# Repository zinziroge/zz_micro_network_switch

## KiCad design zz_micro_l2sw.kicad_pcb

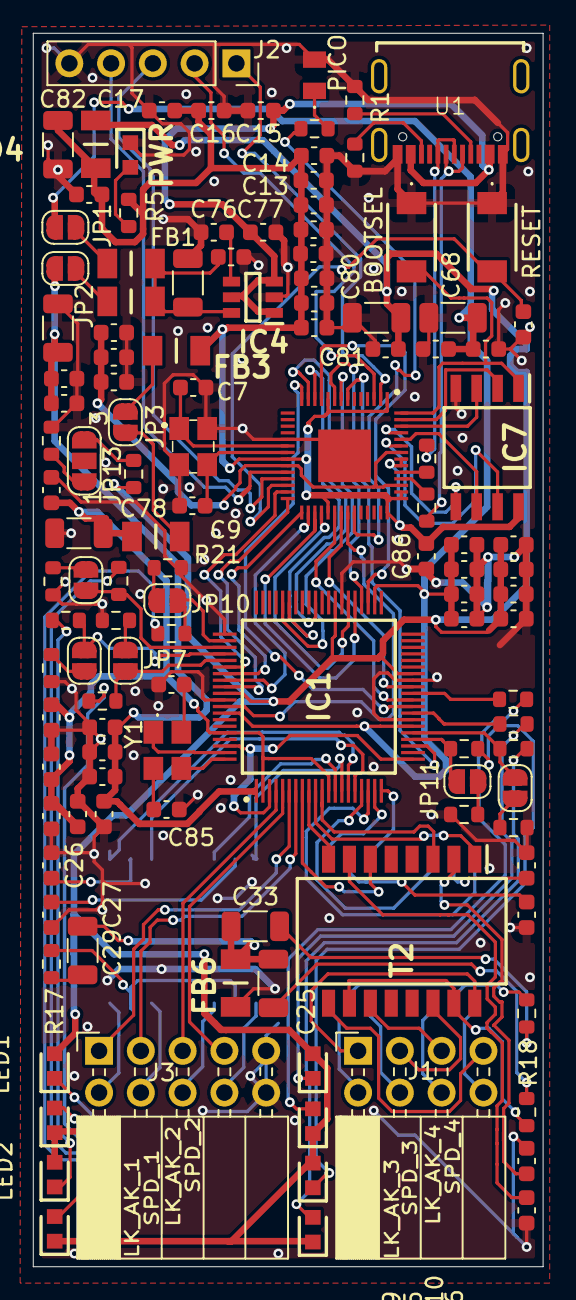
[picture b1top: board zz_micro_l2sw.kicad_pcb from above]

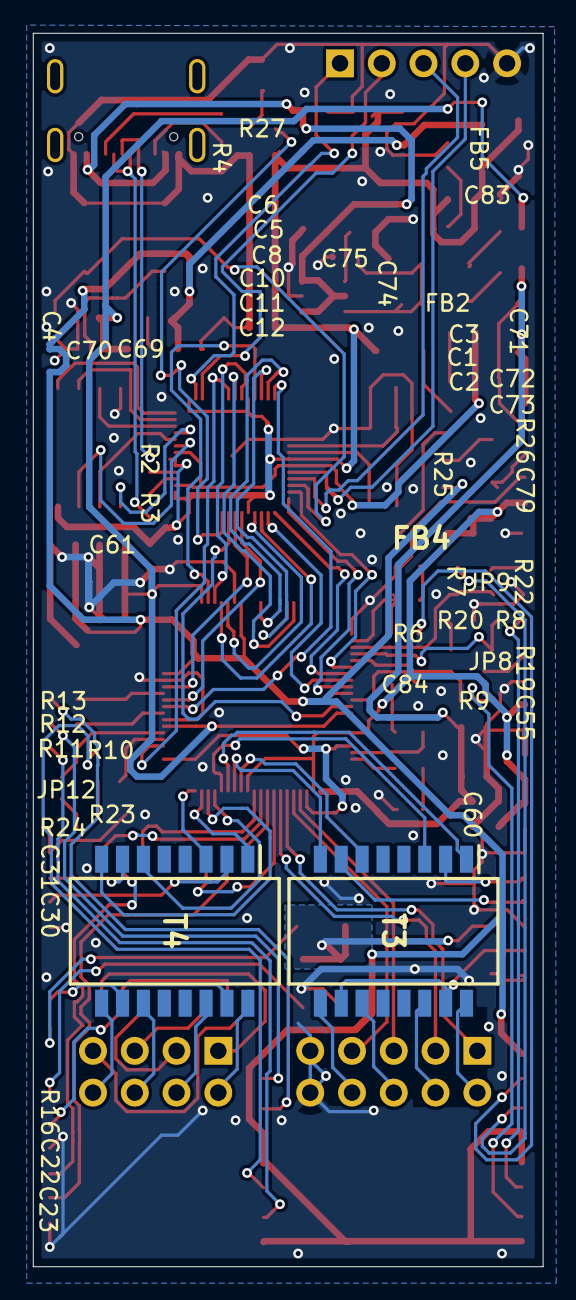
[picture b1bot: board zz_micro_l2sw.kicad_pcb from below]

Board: 2 copper layers, 31.0 x 75.0 mm, 127 parts (2 on the bottom side), 122 nets.

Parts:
C1, C2, C4, C6, C8, C10, C11, C12, C13, C14, C86: 100nF; C_0603_1608Metric
C3, C5: 1uF; C_0603_1608Metric
C7, C9: 18pF; C_0603_1608Metric
C15, C16, C17: 10uF; C_0603_1608Metric
C22, C23, C26, C27, C30, C52, C53, C54, C57, C58, C59, C62, C63, C64, C65, C66, C67, C69, C72, C75, C77, C79, C81, C83: 0.1uF; C_0603_1608Metric
C25, C29, C33: 1nF/2kV; C_1206_3216Metric
C31: 0/1uF; C_0603_1608Metric
C55, C56, C60, C61: 22uF/6.3V; C_0603_1608Metric
C68, C71, C74, C78, C80, C82: 100uF/6.3V; C_1206_3216Metric
C70, C73, C76: 0.01uF; C_0603_1608Metric
C84, C85: 22pF; C_0603_1608Metric
FB1, FB2, FB3, FB4, FB5, FB6: HI1206N101R-00; BEADC3216X130N
IC1: KSZ8795CLXIC; QFP40P1200X1200X160-80N
IC4: MIC5309-1.2YD6; SOT95P280X100-6N
IC5: RP2040; QFN40P700X700X90-57N-D
IC7: W25Q128JVSIQ; SOIC127P790X216-8N
J1: Conn_02x04_Top_Bottom; PinSocket_2x04_P2.54mm_Horizontal
J2: Conn_01x05; PinSocket_1x05_P2.54mm_Vertical
J3: Conn_02x05_Top_Bottom; PinSocket_2x05_P2.54mm_Horizontal
JP1, JP2, JP3, JP7, JP8, JP9, JP10, JP11, JP12: SolderJumper-2_P1.3mm_Open_RoundedPad1.0x1.5mm
JP13: SolderJumper-3_P1.3mm_Open_RoundedPad1.0x1.5mm_NumberLabels
LED1: SPD_2; LEDC1608X70N
LED2: SPD_1; LEDC1608X70N
LED3: PICO; KT0805G
LED4: PWR; LEDC1608X70N
LED5: SPD_3; LEDC1608X70N
LED6: SPD_4; LEDC1608X70N
LED7: LK_AK_2; LEDC1608X70N
LED8: LK_AK_1; LEDC1608X70N
LED9: LK_AK_3; LEDC1608X70N
LED10: LK_AK_4; LEDC1608X70N
R1, R4: 5.1k; R_0603_1608Metric
R2, R3: 27; R_0603_1608Metric
R5, R6, R7, R8, R9, R10, R11, R12, R13, R27: 470; R_0603_1608Metric
R16, R17, R18: 75; R_0603_1608Metric
R19, R20, R21, R22, R23, R24: 750; R_0603_1608Metric
R25: 4.7k; R_0603_1608Metric
R26: 330; R_0603_1608Metric
S1: RESET; TS1088AR02016
S2: BOOTSEL; TS1088AR02016
T2, T3, T4: H1102NL; SOIC127P940X597-16N
U1: TYPE-C 16PIN 2MD(073)
Y1: X322525MOB4SI
Y4: 12MHz; X322512MSB4SI

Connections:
CRSDV5: IC1.51 (RXDV5/__CRSDV5/__RXD5_CTL), IC5.13 (GPIO10)
D_N: R3.1, U1.A7 (DN1), U1.B7 (DN2)
D_P: R2.1, U1.A6 (DP1), U1.B6 (DP2)
GND: C1.2, C2.2, C3.2, C4.1, C5.2, C6.2, C7.2, C8.2, C9.2, C10.2, C11.2, C12.2, C13.2, C14.2, C15.2, C16.2, C17.2, C22.2, C23.2, C26.2, C27.2, C30.2, C31.2, C52.2, C53.2, C54.2, C55.2, C56.2, C57.2, C58.2, C59.2, C60.2, C61.2, C62.2, C63.2, C64.2, C65.2, C66.2, C67.2, C68.2, C69.2, C70.2, C71.2, C72.2, C73.2, C74.2, C75.2, C76.2, C77.2, C78.2, C79.2, C80.2, C81.2, C82.2, C83.2, C84.2, C85.2, C86.2, FB6.1, IC1.27 (GNDD_1), IC1.33 (GNDD_2), IC1.47 (GNDD_3), IC1.61 (GNDD_4), IC1.71 (GNDD_5), IC4.2 (GND), IC5.19 (TESTEN), IC5.57 (GND), IC7.4 (GND), J2.5, J3.5, J3.10, LED3.2 (K), LED4.1 (K), R1.2, R4.2, R19.2, R20.2, R21.2, R22.2, R23.2, R24.2, R26.1, S1.1 (COM), S2.1 (COM), U1.A1 (GND_1), U1.B1 (GND_2), Y4.2 (GND_1), Y4.4 (GND_2)
GNDA: IC1.3 (GNDA_1), IC1.21 (GNDA_2), IC1.78 (GNDA_3)
GNDS: C25.2, C29.2, C33.2, FB6.2
INTR_N_KSZ8795: IC1.23 (INTR_N), IC5.7 (GPIO5)
KSZ8795_XI: IC1.79 (XI), Y1.1 (CRYSTAL__1)
KSZ8795_XO: IC1.80 (XO), Y1.3 (CRYSTAL__2)
LED1_0: IC1.65 (LED1_0), JP7.1 (A), R9.1
LED1_1: IC1.64 (LED1_1), JP8.1 (A), R8.1
LED2_0: IC1.63 (LED2_0), JP9.1 (A), R7.1
LED2_1: IC1.62 (LED2_1), JP10.1 (A), R6.1
LED3_0: IC1.25 (LED3_0), JP11.1 (A), R11.1
LED3_1: IC1.24 (LED3_1), JP12.1 (A), R10.1
LED4_0: IC1.31 (LED4_0), R13.1
LED4_1: IC1.28 (LED4_1), R12.1
unnamed: C25.1, R16.2
unnamed: C29.1, R17.2
unnamed: C33.1, R18.2
unnamed: C76.1, IC4.4 (BYP/ADJ)
unnamed: C74.1, C75.1, FB1.1, FB2.1, IC4.6 (VOUT)
unnamed: IC5.46 (USB_DM), R3.2
unnamed: IC5.47 (USB_DP), R2.2
unnamed: J1.1, T2.16 (TX+)
unnamed: J1.2, T2.14 (TX-)
unnamed: J1.3, T2.11 (RX+)
unnamed: J1.4, T2.9 (RX-)
unnamed: J1.5, T4.16 (TX+)
unnamed: J1.6, T4.14 (TX-)
unnamed: J1.7, T4.11 (RX+)
unnamed: J1.8, T4.9 (RX-)
unnamed: J3.6, T3.16 (TX+)
unnamed: J3.7, T3.14 (TX-)
unnamed: J3.8, T3.11 (RX+)
unnamed: J3.9, T3.9 (RX-)
unnamed: FB1.2, JP1.1 (A)
unnamed: FB2.2, JP2.1 (A)
unnamed: FB3.2, JP3.1 (A)
unnamed: FB4.1, JP3.2 (B)
unnamed: JP7.2 (B), R20.1
unnamed: JP8.2 (B), R19.1
unnamed: JP9.2 (B), R22.1
unnamed: JP10.2 (B), R21.1
unnamed: JP11.2 (B), R24.1
unnamed: JP12.2 (B), R23.1
unnamed: JP13.1 (A), R26.2
unnamed: JP13.3 (B), R25.1
unnamed: LED1.1 (K), R6.2
unnamed: LED2.1 (K), R8.2
unnamed: LED3.1 (A), R27.2
unnamed: LED4.2 (A), R5.2
unnamed: LED5.1 (K), R10.2
unnamed: LED6.1 (K), R12.2
unnamed: LED7.2 (K), R7.2
unnamed: LED8.2 (K), R9.2
unnamed: LED9.2 (K), R11.2
unnamed: LED10.2 (K), R13.2
unnamed: C22.1, T2.2 (CT_1)
unnamed: C23.1, T2.7 (CT_2)
unnamed: R16.1, T2.10 (NC_3), T2.15 (NC_6)
unnamed: C26.1, T3.2 (CT_1)
unnamed: C27.1, T3.7 (CT_2)
unnamed: R17.1, T3.10 (NC_3), T3.15 (NC_6)
unnamed: C30.1, T4.2 (CT_1)
unnamed: C31.1, T4.7 (CT_2)
unnamed: R18.1, T4.10 (NC_3), T4.15 (NC_6)
unnamed: R1.1, U1.A5 (CC1)
unnamed: R4.1, U1.B5 (CC2)
unnamed: C85.1, Y1.2 (GND_1)
unnamed: C84.1, Y1.4 (GND_2)
PME_N: IC1.56 (PME_N), IC5.8 (GPIO6)
QDPL_SD1: IC5.55 (QSPI_SD1), IC7.2 (DO_(IO1))
QSPL_SCLK: IC5.52 (QSPI_SCLK), IC7.6 (CLK)
QSPL_SD0: IC5.53 (QSPI_SD0), IC7.5 (DI_(IO0))
QSPL_SD2: IC5.54 (QSPI_SD2), IC7.3 (/WP_(IO2))
QSPL_SD3: IC5.51 (QSPI_SD3), IC7.7 (/HOLD_OR_/RESET_(IO3))
QSPL_SS: IC5.56 (QSPI_SS_N), IC7.1 (/CS), S2.2 (NO)
REFCLKI: IC1.43 (TXC5/__REFCLKI/__GTXC5), IC5.11 (GPIO8)
REFCLKO: IC1.55 (REFCLKO), IC5.12 (GPIO9)
RESET_N: C4.2, IC5.26 (RUN), S1.2 (NO)
RP2040_LED: IC5.37 (GPIO25), R27.1
RSTn_KSZ8795: IC1.72 (RST_N), IC5.36 (GPIO24)
RX0: IC5.3 (GPIO1), J2.2
RXC5: IC1.44 (RXC5/__GRXC5), IC5.9 (GPIO7)
RXD5_0: IC1.45 (RXD5_0), IC5.31 (GPIO20)
RXD5_1: IC1.46 (RXD5_1), IC5.32 (GPIO21)
RXM1: IC1.5 (RXM1), J3.4
RXM2: IC1.9 (RXM2), T2.8 (RD-)
RXM3: IC1.14 (RXM3), T3.8 (RD-)
RXM4: IC1.18 (RXM4), T4.8 (RD-)
RXP1: IC1.4 (RXP1), J3.3
RXP2: IC1.8 (RXP2), T2.6 (RD+)
RXP3: IC1.13 (RXP3), T3.6 (RD+)
RXP4: IC1.17 (RXP4), T4.6 (RD+)
SPI0_CSn: IC1.69 (SPIS_N), IC5.28 (GPIO17)
SPI0_RX: IC1.66 (SPIQ), IC5.27 (GPIO16)
SPI0_SCK: IC1.67 (SCL_MDC), IC5.29 (GPIO18)
SPI0_TX: IC1.68 (SDA_MDIO), IC5.30 (GPIO19)
SWCLK: IC5.24 (SWCLK), J2.4
SWD: IC5.25 (SWDIO), J2.3
TX0: IC5.2 (GPIO0), J2.1
TXD5_0: IC1.30 (TXD5_0), IC5.34 (GPIO22)
TXD5_1: IC1.32 (TXD5_1), IC5.35 (GPIO23)
TXEN5: IC1.29 (TXEN5/__TXD5_CTL), IC5.14 (GPIO11)
TXM1: IC1.7 (TXM1), J3.2
TXM2: IC1.11 (TXM2), T2.3 (TD-)
TXM3: IC1.16 (TXM3), T3.3 (TD-)
TXM4: IC1.20 (TXM4), T4.3 (TD-)
TXP1: IC1.6 (TXP1), J3.1
TXP2: IC1.10 (TXP2), T2.1 (TD+)
TXP3: IC1.15 (TXP3), T3.1 (TD+)
TXP4: IC1.19 (TXP4), T4.1 (TD+)
VDD5D: C15.1, C77.1, IC4.1 (VIN), IC4.3 (BIAS), IC4.5 (EN), U1.A4 (VBUS_1), U1.B4 (VBUS_2)
VDD11D: C1.1, C2.1, C3.1, IC5.23 (DVDD_1), IC5.45 (VREG_VOUT), IC5.50 (DVDD_2)
VDD12A: C60.1, C62.1, C64.1, C66.1, C71.1, C72.1, C73.1, IC1.1 (VDD12A), JP2.2 (B)
VDD12D: C61.1, C63.1, C65.1, C67.1, C68.1, C69.1, C70.1, IC1.26 (VDD12D_1), IC1.42 (VDD12D_2), IC1.73 (VDD12D_3), JP1.2 (B)
VDD33D: C5.1, C6.1, C8.1, C10.1, C11.1, C12.1, C13.1, C14.1, C16.1, C17.1, C82.1, C83.1, C86.1, FB3.1, FB5.1, IC5.1 (IOVDD_1), IC5.10 (IOVDD_2), IC5.22 (IOVDD_3), IC5.33 (IOVDD_4), IC5.42 (IOVDD_5), IC5.43 (ADC_AVDD), IC5.44 (VREG_VIN), IC5.48 (USB_VDD), IC5.49 (IOVDD_6), IC7.8 (VCC), R5.1
VDDAT33: C52.1, C53.1, C54.1, C55.1, C78.1, C79.1, FB4.2, IC1.2 (VDDAT_1), IC1.12 (VDDAT_2), IC1.76 (VDDAT_3)
VDDIO: C56.1, C57.1, C58.1, C59.1, C80.1, C81.1, FB5.2, IC1.34 (VDDIO_1), IC1.48 (VDDIO_2), IC1.70 (VDDIO_3), LED1.2 (A), LED2.2 (A), LED5.2 (A), LED6.2 (A), LED7.1 (A), LED8.1 (A), LED9.1 (A), LED10.1 (A), R25.2
XIN: C7.1, IC5.20 (XIN), Y4.1 (CRYSTAL_1)
XOUT: C9.1, IC5.21 (XOUT), Y4.3 (CRYSTAL_2)

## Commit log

2025-08-30 add schematics
2025-11-01 modify
